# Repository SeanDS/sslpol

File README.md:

# sslpol
Point of load DC-DC converter for powering a Raspberry Pi Zero and peripherals.

This circuit contains a Texas Instruments LMR33640 synchronous buck converter to convert a 6-36 VDC input to a
(nominally) 5 VDC @ up to 4 A output. The design is based on datasheet recommendations. It also includes a
footprint for a Raspberry Pi Zero to be attached on the rear side, face-down, and the 5 VDC rail provides it
with power. This allows a Raspberry Pi and a large external load (such as a string of LEDs) to be powered
from one supply, overcoming the 500 mA current limit from the Pi's 5 VDC rail.

## Features
- 1-24 VDC @ up to 4 A output, configurable via resistors
- 3.8-36 VDC input range
- Header for a Raspberry Pi Zero with its 5 VDC rail attached to the output of the converter (warning: only use
  a Raspberry Pi when the output is configured to be 5 VDC, via R2 and R3)
- Headers for attached devices using SPI, I2C and FTDI protocols
- Converter pin compatibility with the LMR33610, LMR33620, LMR33630, LMR36510 and LMR36520
- Small footprint 30 × 65 mm board

## Schematic

## Board

## Credits
Sean Leavey  
https://attackllama.com/

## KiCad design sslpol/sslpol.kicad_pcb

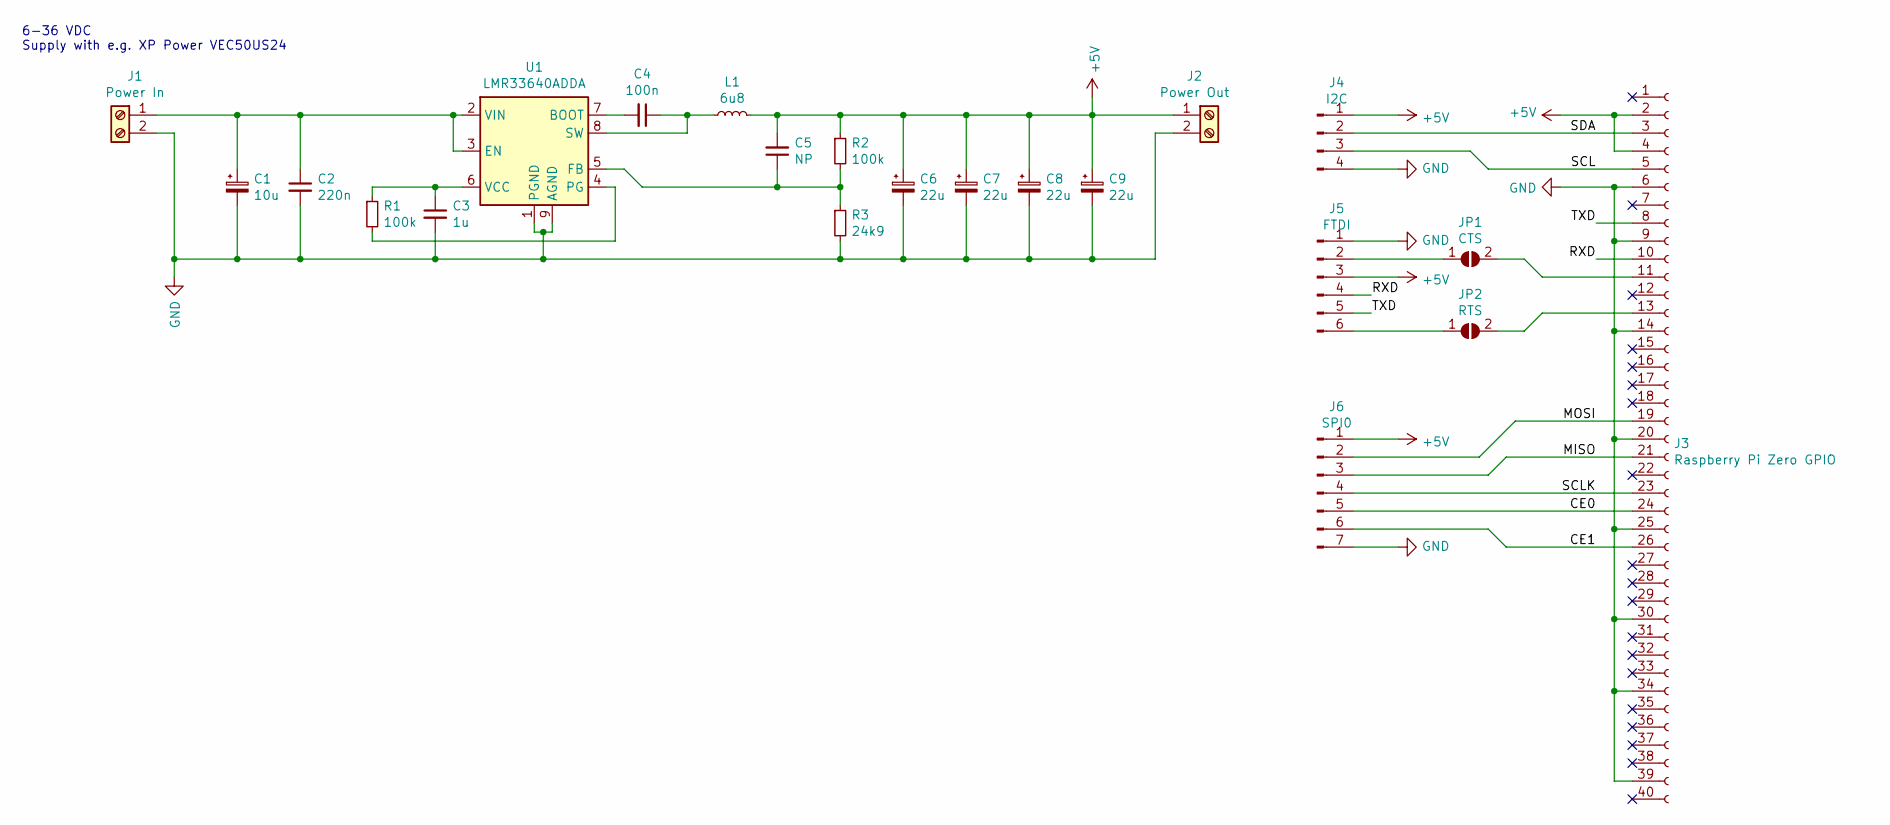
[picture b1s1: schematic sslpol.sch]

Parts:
C1: 10u; CP_Radial_D5.0mm_P2.00mm
C2: 220n; C_0805_2012Metric
C3: 1u; C_0805_2012Metric
C4: 100n; C_0805_2012Metric
C5: NP; C_0805_2012Metric
C6, C7, C8, C9: 22u; CP_Radial_D6.3mm_P2.50mm; MPN1 ESY226M063AE3AA
J1: Power In; TerminalBlock_Phoenix_MKDS-3-2-5.08_1x02_P5.08mm_Horizontal
J2: Power Out; TerminalBlock_Phoenix_MKDS-3-2-5.08_1x02_P5.08mm_Horizontal
J3: Raspberry Pi Zero GPIO; Raspberry_Pi_Zero_Socketed_THT_FaceDown_MountingHoles
J4: I2C; PinHeader_1x04_P1.27mm_Vertical
J5: FTDI; PinHeader_1x06_P1.27mm_Vertical
J6: SPI0; PinHeader_1x07_P1.27mm_Vertical
JP1: CTS; SolderJumper-2_P1.3mm_Open_RoundedPad1.0x1.5mm
JP2: RTS; SolderJumper-2_P1.3mm_Open_RoundedPad1.0x1.5mm
L1: 6u8; L_Bourns_SRP7028A_7.3x6.6mm; MPN1 SRP7028C-6R8M
R1, R2: 100k; R_0805_2012Metric
R3: 24k9; R_0805_2012Metric
U1: LMR33640ADDA; Texas_HSOP-8-1EP_3.9x4.9mm_P1.27mm_ThermalVias

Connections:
+5V: C5.2, C6.1, C7.1, C8.1, C9.1, J2.1, J3.2, J3.4, J4.1, J5.3, J6.1, L1.2, R2.1
/CE0: J3.24, J6.5
/CE1: J3.26, J6.6
/MISO: J3.21, J6.3
/MOSI: J3.19, J6.2
/RXD: J3.10, J5.4
/SCL: J3.5, J4.3
/SCLK: J3.23, J6.4
/SDA: J3.3, J4.2
/TXD: J3.8, J5.5
GND: C1.2, C2.2, C3.2, C6.2, C7.2, C8.2, C9.2, J1.2, J2.2, J3.6, J3.9, J3.14, J3.20, J3.25, J3.30, J3.34, J3.39, J4.4, J5.1, J6.7, R3.2, U1.1 (PGND), U1.9 (AGND)
unnamed: C1.1, C2.1, J1.1, U1.2 (VIN), U1.3 (EN)
unnamed: C3.1, R1.1, U1.6 (VCC)
unnamed: C4.1, L1.1, U1.8 (SW)
unnamed: C4.2, U1.7 (BOOT)
unnamed: C5.1, R2.2, R3.1, U1.5 (FB)
unnamed: J3.11, JP1.2 (B)
unnamed: J3.13, JP2.2 (B)
unnamed: J5.2, JP1.1 (A)
unnamed: J5.6, JP2.1 (A)
unnamed: R1.2, U1.4 (PG)

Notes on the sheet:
6-36 VDC Supply with e.g. XP Power VEC50US24

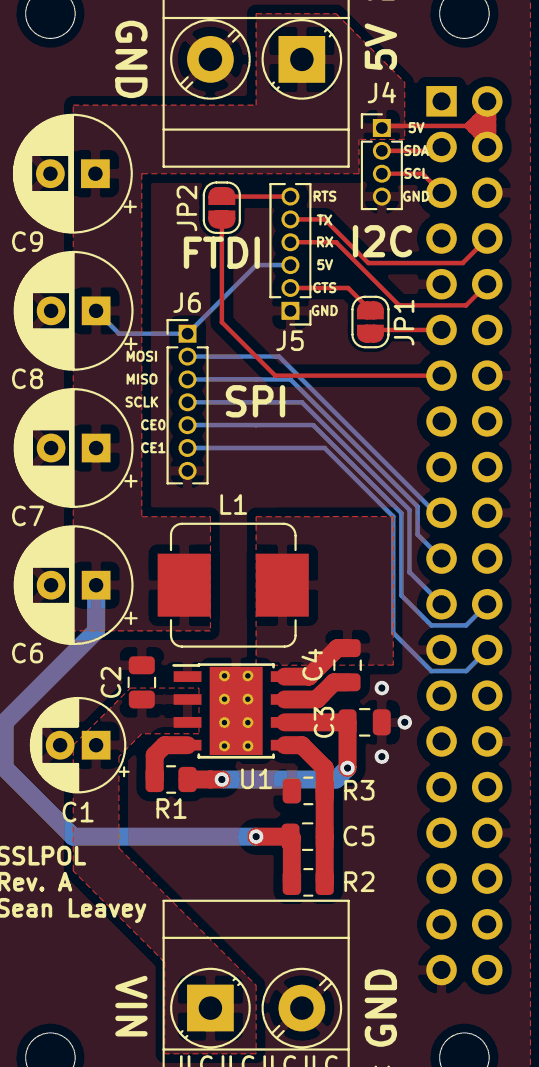
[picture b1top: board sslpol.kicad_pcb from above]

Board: 2 copper layers, 22 parts (1 on the bottom side), 21 nets.

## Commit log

2020-12-30 Board revision A
2020-12-30 Create LICENSE
